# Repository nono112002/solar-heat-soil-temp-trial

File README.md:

# 太陽熱養生 温度測定プロジェクト

太陽熱を利用した土壌養生（消毒）の効果を「感覚」ではなく「データ」で検証する。
畑の複数地点・複数深度に温度センサーを設置し、リアルタイムで計測・記録・可視化するIoTシステム。

---

## システム概要図

### データの流れ

1. **農場の PicoBox（3台）** が30分ごとに温度を計測
2. **カシムラ モバイルルータ**（SORACOM SIM）経由で WiFi → LTE でインターネットに出る
3. **Google Cloud（GCE）上の Mosquitto** が MQTT メッセージを受信
4. **GCE の mqtt_logger** が SQLite に保存 + **Flask API** で配信
5. **自宅の Raspberry Pi** も GCE の MQTT を購読し、ローカル SQLite に保存
6. **Grafana**（ラズパイ）と **ポートフォリオHP**（GitHub Pages）でグラフ表示

> データは GCE（API配信用）と自宅ラズパイ（Grafana用）の2箇所に保存される。

---

## ブラウザからの確認方法

自宅 LAN 内のPCから以下にアクセス：

| 画面 | URL | 内容 |
|---|---|---|
| Grafana ダッシュボード | http://192.168.0.10:3000 | Zone-A/B/C の温度グラフ（メインの確認画面） |
| ポートフォリオ HP | http://192.168.0.10:1313 | プロジェクト紹介ページ |
| ライブデータ（3分割） | http://192.168.0.10:1313/dashboard.html | Grafana の3パネルを iFrame で一覧表示 |

> Grafana は匿名アクセス有効（ログイン不要）。ポートフォリオ HP（Hugo）は手動起動が必要（後述）。

---

## ハードウェア構成

### PicoBox（3台共通）

| 部材 | 仕様 | 数量 |
|---|---|---|
| Raspberry Pi Pico W | RP2040 + CYW43439 | 3 |
| 温度センサー | DS18B20（防水型） | 21（7本 × 3台） |
| PCB（PicoBox） | JLCPCB 発注・自作基板 | 3 |
| SDカード | ローカルバックアップ用 | 3 |
| 防水BOX | 屋外設置用 | 3 |

### GPIO 割り当て（3台共通）

| 機能 | GPIO |
|---|---|
| DS18B20 × 7（S1〜S7） | GP8〜GP14 |
| SDカード（SPI） | GP2〜GP5、CD=GP6 |
| TX LED | GP15 |
| 主電源監視（ADC） | GP26 |

### センサー配置（1台あたり7本）

| ラベル | 位置 | 深さ |
|---|---|---|
| S1_center_10cm | 中央 | 10cm |
| S2_center_25cm | 中央 | 25cm |
| S3_center_40cm | 中央 | 40cm |
| S4_edge_10cm | エッジ | 10cm |
| S5_edge_25cm | エッジ | 25cm |
| S6_edge_40cm | エッジ | 40cm |
| S7_outdoor | 外気温 | — |

### ゾーン区分

| ゾーン | 区 | 処理内容 |
|---|---|---|
| zone-a | 区A | 標準区（たい肥＋菌＋ビニール） |
| zone-b | 区B | 対照・菌なし（たい肥＋ビニール） |
| zone-c | 区C | 対照・ビニールなし（たい肥のみ） |

### PicoBox ↔ ゾーン対応

| PicoBox筐体 | config.py ZONE | 設置エリア |
|---|---|---|
| ユニット3 | `zone-a` | 区A（標準区） |
| ユニット2 | `zone-b` | 区B（対照・菌なし） |
| ユニット1 | `zone-c` | 区C（対照・ビニールなし） |

> 筐体番号と区が一致しないが、config.py の ZONE で正しいゾーン名を送信するため
> DB上は常に物理エリアと一致する。

### 通信機器

| 機器 | 型番 | 役割 |
|---|---|---|
| モバイルルータ | カシムラ KD-249 | PicoBox の WiFi アクセスポイント → LTE 接続 |
| SIM | SORACOM Air plan-K2（KDDI） | モバイルデータ通信（月500MB、実使用量 約1.1MB/月） |

---

## サーバー構成（Raspberry Pi 4）

| コンポーネント | バージョン | 役割 | 自動起動 |
|---|---|---|---|
| mqtt_logger.py | Python 3.13 / paho-mqtt 2.1.0 | GCE の MQTT を購読 → SQLite に保存 | systemd ✅ |
| SQLite | 3.46.1 | データ保存（/var/lib/solar-heat/data.db） | — |
| Grafana | 13.0.1 + frser-sqlite-datasource | データ可視化（:3000） | systemd ✅ |
| Mosquitto | 2.0.21 | ローカル MQTT ブローカー（現在未使用） | systemd ✅ |
| Hugo | 0.131.0 + Blowfish v2.88.1 | ポートフォリオ HP（:1313） | **手動起動** |

### ラズパイの情報

| 項目 | 値 |
|---|---|
| OS | Debian 13 (trixie) aarch64 |
| ホスト名 | hp-server |
| IPアドレス | 192.168.0.10 |
| ストレージ | 28GB（24% 使用） |
| RAM | 3.7GB |

---

## クラウド構成（Google Cloud）

MQTT の中継サーバーとして GCE を使用。農場（モバイル回線）と自宅（固定回線）を繋ぐ。

| 項目 | 値 |
|---|---|
| プロジェクト | solar-heat-mqtt |
| VM名 | mqtt-broker |
| マシンタイプ | e2-micro（無料枠） |
| リージョン | us-central1-a |
| 外部IP | 34.58.138.105 |
| OS | Debian 12 (bookworm) |
| サービス | Mosquitto 2.0.11（:1883、認証あり）、mqtt_logger、Flask API（gunicorn :5000） |
| DB | /var/lib/solar-heat/data.db |
| API | https://34-58-138-105.sslip.io/api/（nginx + certbot SSL） |

---

## ソフトウェア構成

### ファイル一覧

```
solar-heat/
├── README.md                          # 本ファイル
├── pico/
│   ├── main.py                        # Pico W ファームウェア（MicroPython）
│   ├── config.py                      # WiFi/MQTT/ゾーン設定（.gitignore）
│   └── test_power_led.py              # LED テスト用
├── server/
│   ├── README.md                      # Pi セットアップ手順
│   ├── mqtt_logger.py                 # MQTT → SQLite 保存
│   ├── mqtt_logger.service            # systemd ユニットファイル
│   ├── mosquitto/
│   │   └── mosquitto.conf             # MQTT ブローカー設定
│   └── grafana/
│       └── provisioning/
│           ├── datasources/sqlite.yml
│           ├── dashboards/dashboards.yml
│           └── dashboards/solar-heat.json
├── docs/
│   ├── system_overview.png            # システム概要図
│   ├── picobox_diagram.png            # PicoBox 回路構成図
│   ├── server_design.md               # サーバー設計書（詳細）
│   ├── sensor_registry.md             # センサー台帳
│   ├── pcb_spec.md                    # PCB 設計仕様
│   ├── parts.md                       # 部品表
│   └── blog/                          # ブログ記事素材
└── kicad/                             # PCB 設計データ（KiCad）

GCE 上の配置（リポジトリ外、VM 内に直接配置）:
/home/nono/solar-heat/server/mqtt_logger.py  # MQTT ロガー（サービス実行元）
/var/lib/solar-heat/data.db                  # SQLite DB（API配信元）
/etc/systemd/system/mqtt_logger.service
```

### Pico ファームウェアの動作

`pico/main.py` は以下のサイクルを30分ごとに繰り返す：

1. DS18B20 × 7本から温度を読み取り
2. SDカードに CSV で記録（ローカルバックアップ）
3. WiFi ON → カシムラに接続
4. MQTT で GCE に温度データを送信（`solar-heat/{zone}/{label}`）
5. MQTT でデバイスステータスを送信（`solar-heat/{zone}/status`）
6. 電源電圧が 4.0V 未満なら電源アラートを送信
7. WiFi OFF → スリープ（ウォッチドッグタイマー feed しながら）

**ウォッチドッグタイマー**: 8秒タイムアウト。熱暴走等でフリーズした場合に自動リセットする。
起動直後に有効化され、メインループ内の各ステップおよびスリープ中（1秒ごと）に feed する。

### LED 表示パターン

| 状態 | 意味 |
|---|---|
| 消灯 | 正常 |
| 常時点灯 | 電源異常（bus_v < 4.0V） |
| 低速点滅 | SD異常 |
| 高速点滅 | 電源異常 + SD異常 |

### MQTT トピック

| トピック | ペイロード例 |
|---|---|
| `solar-heat/zone-a/S1_center_10cm` | `{"time": "2026-07-12T16:00:00", "temp": 29.88}` |
| `solar-heat/zone-a/status` | `{"zone": "zone-a", "bus_v": 5.02, "sd_status": "ok", "uptime_min": 120}` |
| `solar-heat/zone-a/power_alert` | `{"zone": "zone-a", "bus_v": 3.8, "alert": "main_power_lost"}` |

### SQLite テーブル

| テーブル | カラム | 内容 |
|---|---|---|
| temperature | timestamp, zone, label, temp | 温度データ |
| device_status | zone, bus_v, sd_status, wifi_attempts, uptime_min | デバイス状態 |
| power_alert | zone, bus_v, alert | 電源異常アラート |

---

## セットアップ手順

### 1. Raspberry Pi

詳細は `server/README.md` を参照。

```bash
# リポジトリ取得
cd ~ && git clone https://github.com/nono112002/solar-heat-soil-temp-trial.git solar-heat

# Mosquitto（ローカル、現在未使用だが残してある）
sudo ln -s ~/solar-heat/server/mosquitto/mosquitto.conf /etc/mosquitto/conf.d/solar-heat.conf
sudo systemctl restart mosquitto

# SQLite 保存先
sudo mkdir -p /var/lib/solar-heat && sudo chown nono:nono /var/lib/solar-heat

# mqtt_logger サービス
sudo ln -s ~/solar-heat/server/mqtt_logger.service /etc/systemd/system/mqtt_logger.service
sudo systemctl daemon-reload && sudo systemctl enable --now mqtt_logger

# Grafana（別途 apt で導入済み）
# プラグイン: grafana cli plugins install frser-sqlite-datasource
```

### 2. PicoBox（各台）

```bash
# ファームウェア書き込み（USB 接続状態で）
mpremote connect COMx fs cp pico/main.py :main.py
mpremote connect COMx fs cp pico/config.py :config.py
```

`config.py` は `.gitignore` で管理外。各台で ZONE と SENSOR_PINS を設定する。
リポジトリに `config_pico1.py` / `config_pico2.py` / `config_pico3.py` を用意してある。

```python
# config_example.py を参照。実際の値は config_pico*.py に記入（gitignore対象）
WIFI_SSID     = "your_ssid"
WIFI_PASSWORD = "your_password"
MQTT_BROKER   = "your_mqtt_host"
MQTT_PORT     = 1883
MQTT_USER     = "your_user"
MQTT_PASS     = "your_pass"
ZONE          = "zone-a"  # zone-a / zone-b / zone-c
```

### 3. Hugo（ポートフォリオ HP）

```bash
# ラズパイで実行
cd ~ && git clone https://github.com/nono112002/nono112002.github.io.git portfolio
cd portfolio && git submodule update --init --recursive

# 起動（手動）
hugo server --bind 0.0.0.0 --baseURL http://192.168.0.10 -p 1313
```

### 4. Google Cloud（MQTT 中継 + バックアップ）

```bash
# gcloud CLI でセットアップ済み
# プロジェクト: solar-heat-mqtt
# VM: mqtt-broker (e2-micro, us-central1-a)
# Mosquitto 認証: server/.env を参照
# ファイアウォール: tcp:1883 を開放

# バックアップロガー
# /opt/solar-heat/mqtt_logger.py — ローカル Mosquitto を購読し SQLite に保存
# /var/lib/solar-heat/data.db — ラズパイと同一スキーマのバックアップDB
# systemd: mqtt_logger.service（自動起動）
```

---

## 運用コマンド集

### ラズパイ（SSH: `ssh nono@192.168.0.10`）

```bash
# ログ確認
journalctl -u mqtt_logger -f

# MQTT 受信状況をリアルタイム確認
mosquitto_sub -h $MQTT_HOST -u $MQTT_USER -P $MQTT_PASS -t 'solar-heat/#' -v

# DB 確認
sqlite3 /var/lib/solar-heat/data.db 'SELECT * FROM temperature ORDER BY id DESC LIMIT 10;'
sqlite3 /var/lib/solar-heat/data.db 'SELECT zone, COUNT(*) FROM temperature GROUP BY zone;'

# ソフト更新
cd ~/solar-heat && git pull && sudo systemctl restart mqtt_logger

# Hugo 起動
cd ~/portfolio && git pull --recurse-submodules
hugo server --bind 0.0.0.0 --baseURL http://192.168.0.10 -p 1313
```

### GCE（`gcloud compute ssh mqtt-broker --zone=us-central1-a`）

```bash
# Mosquitto ログ確認
sudo journalctl -u mosquitto -f

# 接続テスト
mosquitto_pub -h localhost -u $MQTT_USER -P $MQTT_PASS -t test/hello -m "test"

# バックアップロガー確認
sudo journalctl -u mqtt_logger -f
sqlite3 /var/lib/solar-heat/data.db 'SELECT * FROM temperature ORDER BY id DESC LIMIT 10;'
```

---

## ブログ記事

| 回 | タイトル | URL |
|---|---|---|
| 第1回 | 太陽熱養生とは / 実験設計 | https://note.com/nono399/ |
| 第2回 | 回路設計・PCB発注 | https://note.com/nono399/ |
| 第3回 | ファームウェアと自宅サーバー | https://note.com/nono399/n/nedf561051aac |

---

## 詳細ドキュメント

| ドキュメント | 内容 |
|---|---|
| [サーバー設計書](docs/server_design.md) | ラズパイの詳細構成・配置・ハマりポイント |
| [センサー台帳](docs/sensor_registry.md) | 各 Pico のセンサー割り当て・DS18B20 ID |
| [PCB 設計仕様](docs/pcb_spec.md) | PicoBox 基板の設計仕様 |
| [部品表](docs/parts.md) | 購入部品一覧 |

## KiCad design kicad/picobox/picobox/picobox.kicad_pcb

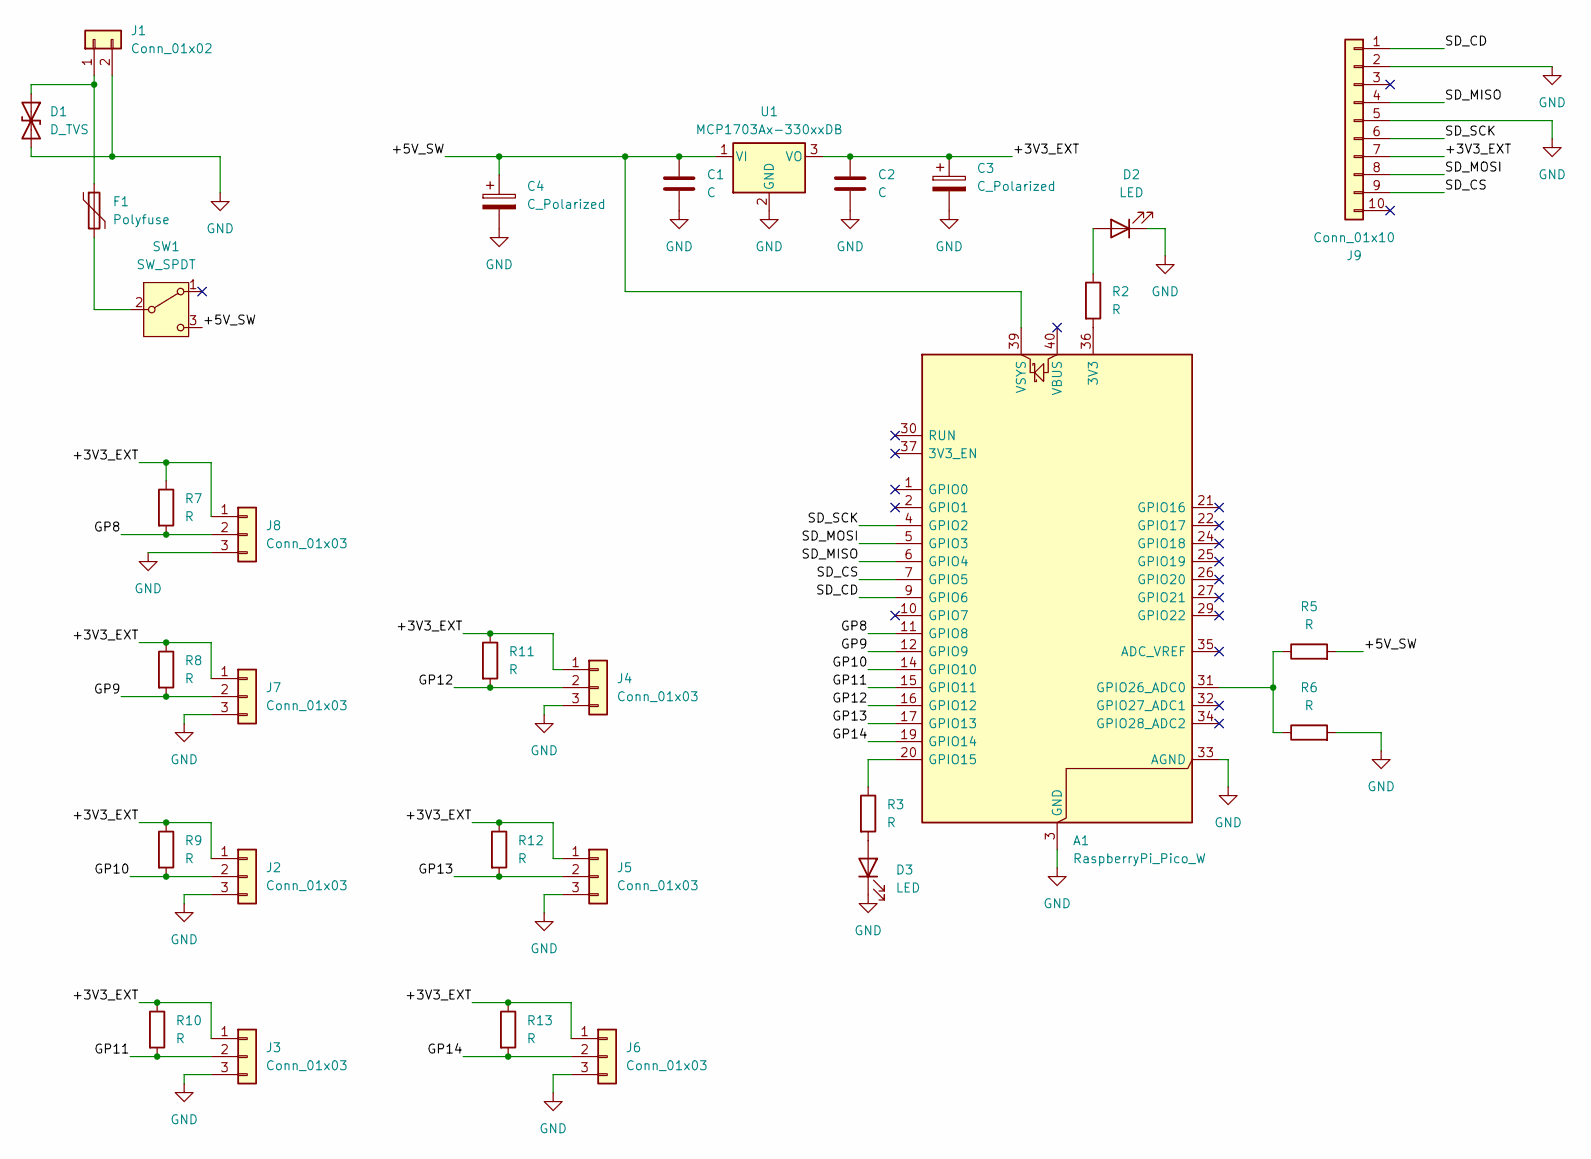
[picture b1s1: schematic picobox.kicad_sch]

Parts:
A1: RaspberryPi_Pico_W; RaspberryPi_Pico_Common_THT
C1, C2: C; C_Disc_D5.0mm_W2.5mm_P5.00mm
C3: C_Polarized; CP_Radial_D5.0mm_P2.00mm
C4: C_Polarized; CP_Radial_D6.3mm_P2.50mm
D1: D_TVS; D_DO-201AD_P15.24mm_Horizontal
D2, D3: LED; LED_D3.0mm
F1: Polyfuse; RV_Disc_D9mm_W3.4mm_P5mm
J1: Conn_01x02; PhoenixContact_SPT_1.5_2-H-3.5_1x02_P3.5mm_Horizontal
J2, J3, J4, J5, J6, J7, J8: Conn_01x03; JST_PH_B3B-PH-K_1x03_P2.00mm_Vertical
J9: Conn_01x10; PinSocket_1x10_P2.54mm_Vertical
R2, R3, R5, R6, R7, R8, R9, R10, R11, R12, R13: R; R_Axial_DIN0207_L6.3mm_D2.5mm_P7.62mm_Horizontal
SW1: SW_SPDT; SW_Slide-03_Wuerth-WS-SLTV_10x2.5x6.4_P2.54mm
U1: MCP1703Ax-330xxDB; SOT-223-3_TabPin2

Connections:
/+3V3_EXT: C2.1, C3.1, J2.1, J3.1, J4.1, J5.1, J6.1, J7.1, J8.1, J9.7, R7.1, R8.1, R9.1, R10.1, R11.1, R12.1, R13.1, U1.3 (VO)
/+5V_SW: A1.39 (VSYS), C1.1, C4.1, R5.2, SW1.3 (C), U1.1 (VI)
/GP8: A1.11 (GPIO8), J8.2, R7.2
/GP9: A1.12 (GPIO9), J7.2, R8.2
/GP10: A1.14 (GPIO10), J2.2, R9.2
/GP11: A1.15 (GPIO11), J3.2, R10.2
/GP12: A1.16 (GPIO12), J4.2, R11.2
/GP13: A1.17 (GPIO13), J5.2, R12.2
/GP14: A1.19 (GPIO14), J6.2, R13.2
/SD_CD: A1.9 (GPIO6), J9.1
/SD_CS: A1.7 (GPIO5), J9.9
/SD_MISO: A1.6 (GPIO4), J9.4
/SD_MOSI: A1.5 (GPIO3), J9.8
/SD_SCK: A1.4 (GPIO2), J9.6
GND: A1.3 (GND), A1.8 (GND), A1.13 (GND), A1.18 (GND), A1.23 (GND), A1.28 (GND), A1.33 (AGND), A1.38 (GND), C1.2, C2.2, C3.2, C4.2, D1.2 (A2), D2.1 (K), D3.1 (K), J1.2, J2.3, J3.3, J4.3, J5.3, J6.3, J7.3, J8.3, J9.2, J9.5, R6.2, U1.2 (GND)
unnamed: A1.36 (3V3), R2.2
unnamed: A1.20 (GPIO15), R3.1
unnamed: A1.31 (GPIO26_ADC0), R5.1, R6.1
unnamed: D1.1 (A1), F1.1, J1.1
unnamed: D2.2 (A), R2.1
unnamed: D3.2 (A), R3.2
unnamed: F1.2, SW1.2 (B)

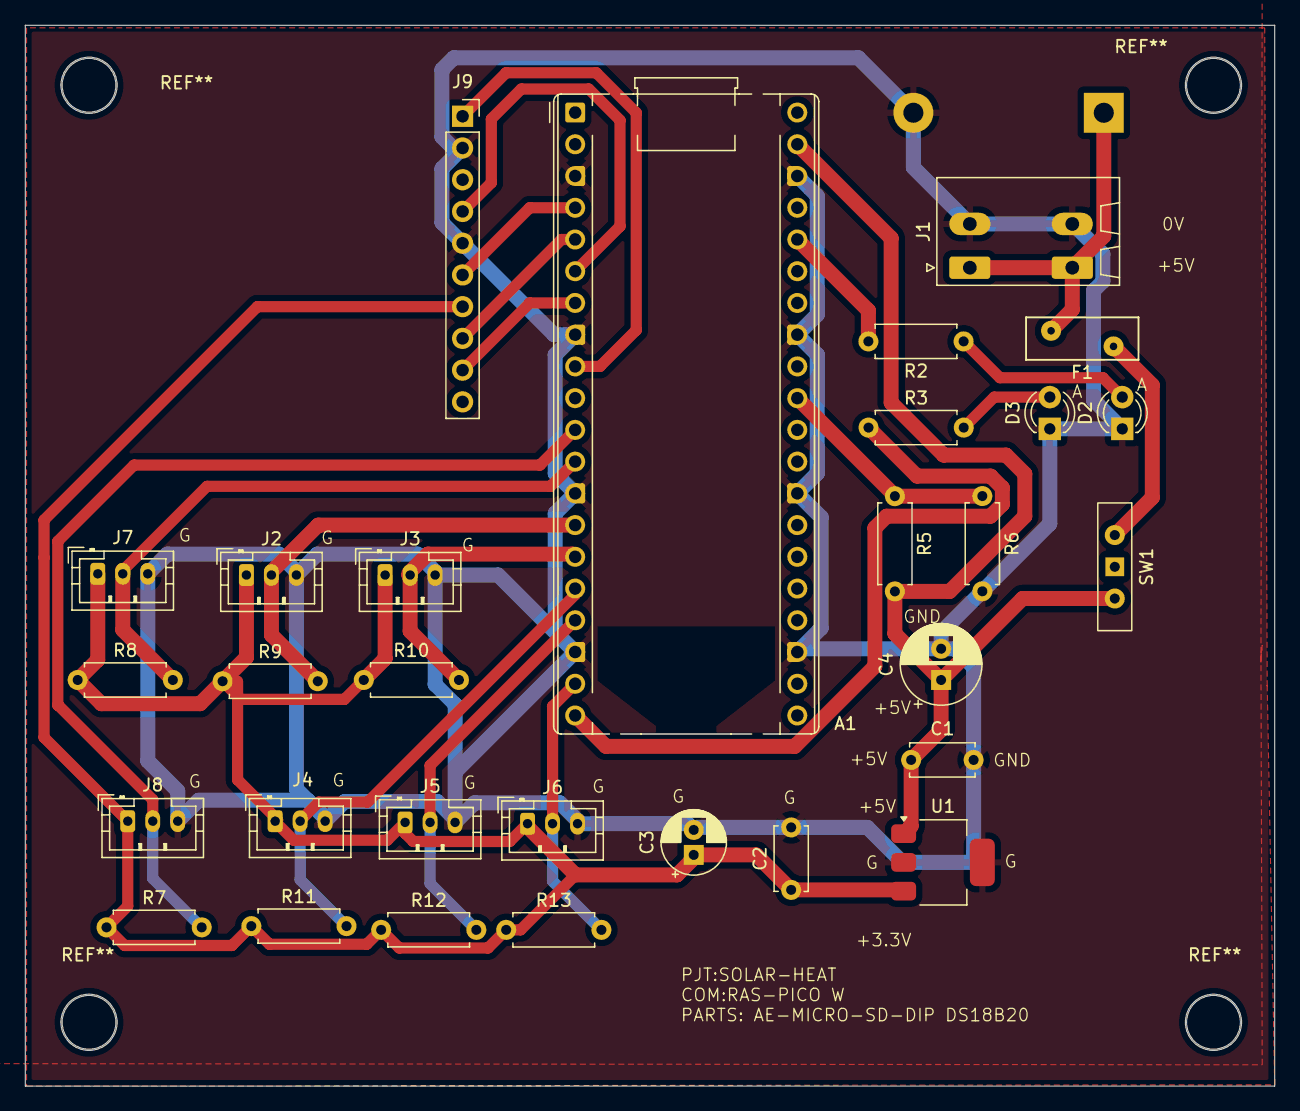
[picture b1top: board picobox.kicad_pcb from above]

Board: 2 copper layers, 100.0 x 84.9 mm, 31 parts (1 on the bottom side), 22 nets.

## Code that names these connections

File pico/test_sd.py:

"""SDカード動作確認テスト
1. カード検出 (GP6)
2. SPIマウント (GP2-5)
3. 書き込み・読み取り
4. ファイル一覧
"""
import machine
import os
import sdcard

PIN_SD_SCK    = 2
PIN_SD_MOSI   = 3
PIN_SD_MISO   = 4
PIN_SD_CS     = 5
PIN_SD_DETECT = 6

# WiFi干渉を避ける
import network
network.WLAN(network.STA_IF).active(False)

print("=== SD Card Test ===")

# 1. カード検出
detect = machine.Pin(PIN_SD_DETECT, machine.Pin.IN, machine.Pin.PULL_UP)
print("[1] Card Detect: GP6 =", detect.value(), "(0=挿入済み, 1=未挿入)")
if detect.value() != 0:
    print("    ERROR: カードが検出されません")
    raise SystemExit

# 2. SPI接続・マウント
print("[2] SPIマウント試行...")
try:
    spi = machine.SPI(0,
        sck=machine.Pin(PIN_SD_SCK),
        mosi=machine.Pin(PIN_SD_MOSI),
        miso=machine.Pin(PIN_SD_MISO))
    sd = sdcard.SDCard(spi, machine.Pin(PIN_SD_CS))
    os.mount(os.VfsFat(sd), "/sd")
    print("    OK: マウント成功")
except Exception as e:
    print("    ERROR:", e)
    raise SystemExit

# 3. 書き込み・読み取り
print("[3] 書き込みテスト...")
test_path = "/sd/_picobox_test.txt"
test_data = "PicoBox SD test OK"
try:
    with open(test_path, "w") as f:
        f.write(test_data)
    with open(test_path, "r") as f:
        readback = f.read()
    if readback == test_data:
        print("    OK: 書き込み・読み取り一致")
    else:
        print("    NG: 不一致 -> ", readback)
except Exception as e:
    print("    ERROR:", e)

# 4. ファイル一覧
print("[4] /sd ファイル一覧:")
for f in os.listdir("/sd"):
    try:
        st = os.stat("/sd/" + f)
        print("    {:10d}  {}".format(st[6], f))
    except:
        print("    ?           ", f)

# テストファイル削除
try:
    os.remove(test_path)
    print("    (テストファイル削除)")
except:
    pass

os.umount("/sd")
print("=== END ===")

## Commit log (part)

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2026-04-20 docs: note記事1本目追加（太陽熱養生・動機記事）
